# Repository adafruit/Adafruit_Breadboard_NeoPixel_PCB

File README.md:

# PCB for the Adafruit Breadboard-able NeoPixels

__Format is EagleCAD schematic and board layout__

<a href="http://www.adafruit.com/products/1312"><br/>Click here to purchase one from the Adafruit shop</a>

This is the easiest way possible to add small, bright RGB pixels to your project. We took the same technology from our Flora NeoPixels and made them breadboard friendly, with two rows of 3 x 0.1" spaced header on each side for easy soldering, chaining and breadboarding. These ultra-bright LEDs have a constant-current driver cooked right into the LED package! The pixels are chainable - so you only need 1 pin/wire to control as many LEDs as you like.

These pixels have full 24-bit color ability with PWM taken care of by the controller chip. Since the LED is so bright, you need less current/power to get the effects you want. The driver is constant current so its OK if your battery power changes or fluctuates a little.

Each pixel draws as much as 60mA (all three RGB LEDs on for full brightness white). An Arduino can drive up to 500 pixels at 30 FPS (it will run out of RAM after that). Using ribbon cable you can string these up to 6" apart (after that, you might get power droops and data corruption)

Each order comes with 4 individually controllable pixels. In the photos above we show the pixels with headers soldered on, but the pixels do not come with any headers. [You can pick up some in the shop if you need](http://adafruit.com/products/392).

[Our detailed NeoPixel Uberguide has everything you need to use NeoPixels in any shape and size. Including ready-to-go library & example code for the Arduino UNO/Duemilanove/Diecimila, Flora/Micro/Leonardo, Trinket/Gemma, Arduino Due & Arduino Mega/ADK (all versions)](http://learn.adafruit.com/adafruit-neopixel-uberguide).

## License

Adafruit invests time and resources providing this open source design, 
please support Adafruit and open-source hardware by purchasing 
products from Adafruit!

Designed by Adafruit Industries.  
Creative Commons Attribution, Share-Alike license, check license.txt for more information
All text above must be included in any redistribution

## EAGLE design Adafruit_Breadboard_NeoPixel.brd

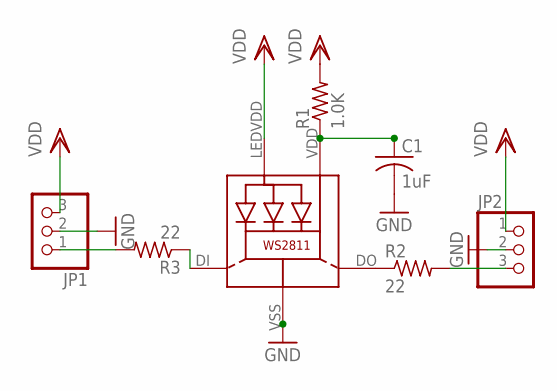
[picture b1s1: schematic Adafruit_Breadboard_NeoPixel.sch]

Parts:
C1: 1uF; C0603K
JP1, JP2: PINHD-1X3CB; 1X03-CLEANBIG
LED1: WS28115050
R1: 1.0K; R0603
R2, R3: 22; R0603

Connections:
GND: C1.2, JP1.2, JP2.2, LED1.VSS (GND)
IN: JP1.1, R3.2
unnamed: LED1.DO, R2.1
unnamed: LED1.DI, R3.1
unnamed: C1.1, LED1.VDD, R1.1
OUT: JP2.3, R2.2
VDD: JP1.3, JP2.1, LED1.LEDVDD, R1.2

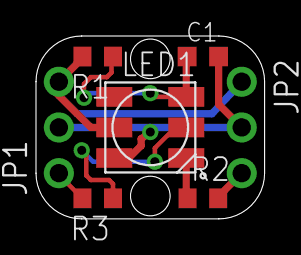
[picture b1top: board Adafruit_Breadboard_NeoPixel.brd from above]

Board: 2 copper layers, 12.7 x 10.2 mm, 8 parts (1 on the bottom side), 7 nets.

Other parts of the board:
U$1: ADAFRUIT_2.5MM

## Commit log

2013-11-02 init
2019-05-08 readme + image

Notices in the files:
parts and their libraries:
microbuilder: This work is placed in the public domain, and may be freely used for commercial and non-commercial work with the following conditions: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
